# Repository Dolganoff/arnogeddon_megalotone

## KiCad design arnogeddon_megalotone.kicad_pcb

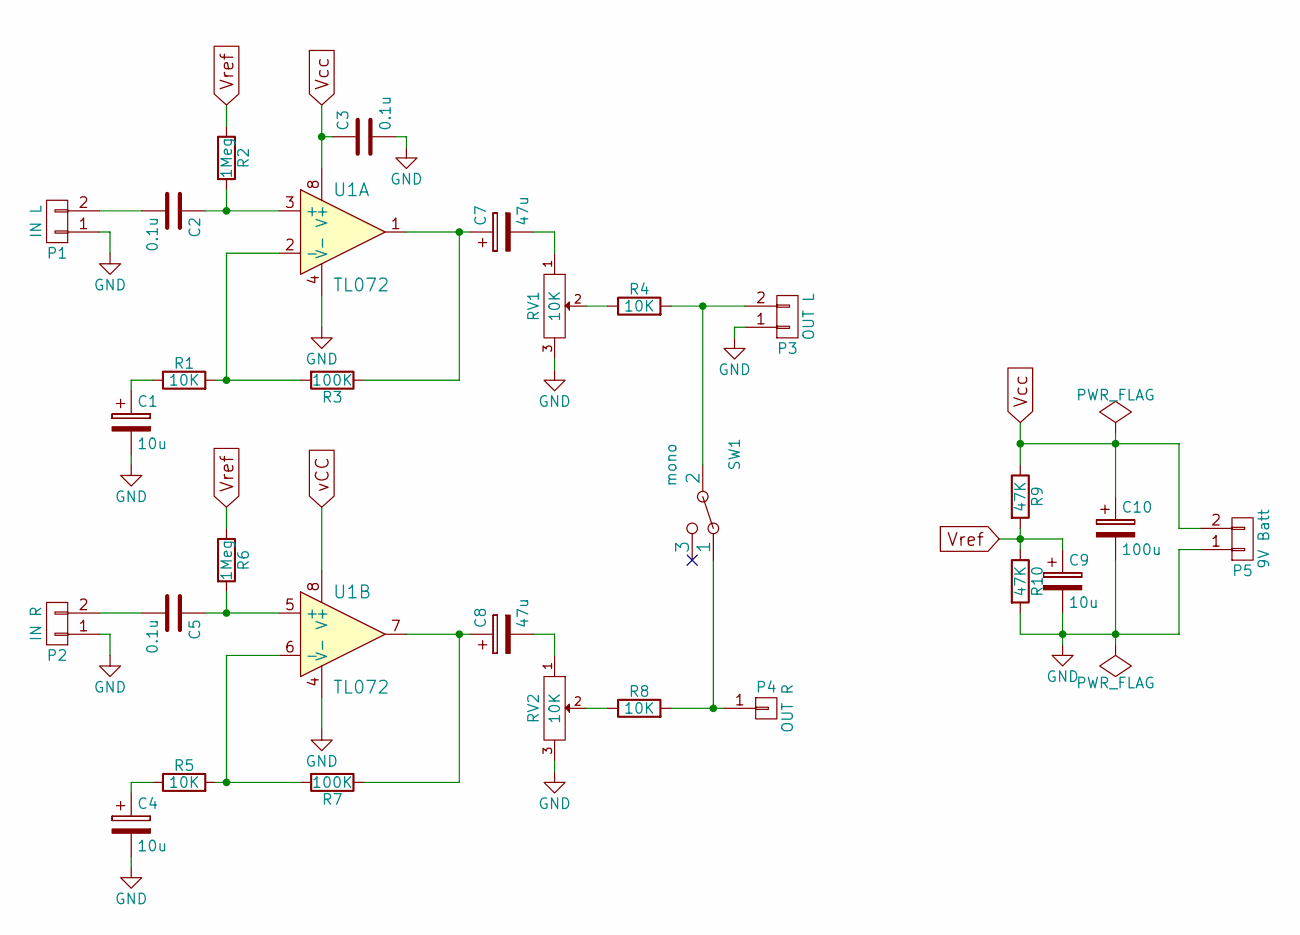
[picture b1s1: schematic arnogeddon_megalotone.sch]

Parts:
C1, C4, C9: 10u; Elko_vert_DM5_RM2-5
C2, C3, C5: 0.1u; Capacitor7x2.5RM5
C7, C8: 47u; Elko_vert_DM6-3_RM2-5
C10: 100u; Elko_vert_DM7-5_RM2-5
P1: IN L; Pin_Header_Straight_1x02
P2: IN R; Pin_Header_Straight_1x02
P3: OUT L; Pin_Header_Straight_1x02
P4: OUT R; Pin_Header_Straight_1x01
P5: 9V Batt; Pin_Header_Straight_1x02
R1, R4, R5, R8: 10K; R3-LARGE_PADS
R2, R6: 1Meg; R3-LARGE_PADS
R3, R7: 100K; R3-LARGE_PADS
R9, R10: 47K; R3-LARGE_PADS
RV1, RV2: 10K; SIL-3-LARGE_PADS
SW1: mono; SIL-3-LARGE_PADS
U1: TL072; DIP-8_LARGE_PADS

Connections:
GND: C1.2, C3.2, C4.2, C9.2, C10.2, P1.1, P2.1, P3.1, P5.1, R10.2, RV1.3, RV2.3, U1.4 (V-)
unnamed: C1.1, R1.1
unnamed: C2.1, R2.2, U1.3 (+)
unnamed: C2.2, P1.2
unnamed: C4.1, R5.1
unnamed: C5.1, R6.2, U1.5 (+)
unnamed: C5.2, P2.2
unnamed: C7.1, R3.1, U1.1
unnamed: C7.2, RV1.1
unnamed: C8.1, R7.1, U1.7
unnamed: C8.2, RV2.1
unnamed: P3.2, R4.2, SW1.2
unnamed: P4.1, R8.2, SW1.1
unnamed: R1.2, R3.2, U1.2 (-)
unnamed: R4.1, RV1.2
unnamed: R5.2, R7.2, U1.6 (-)
unnamed: R8.1, RV2.2
Vcc: C3.1, C10.1, P5.2, R9.1, U1.8 (V+)
Vref: C9.1, R2.1, R6.1, R9.2, R10.1

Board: 2 copper layers, 28 parts (0 on the bottom side), 19 nets, no tracks yet.

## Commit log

2015-12-05 :tada: Added .gitattributes
2021-08-29 latest mods
